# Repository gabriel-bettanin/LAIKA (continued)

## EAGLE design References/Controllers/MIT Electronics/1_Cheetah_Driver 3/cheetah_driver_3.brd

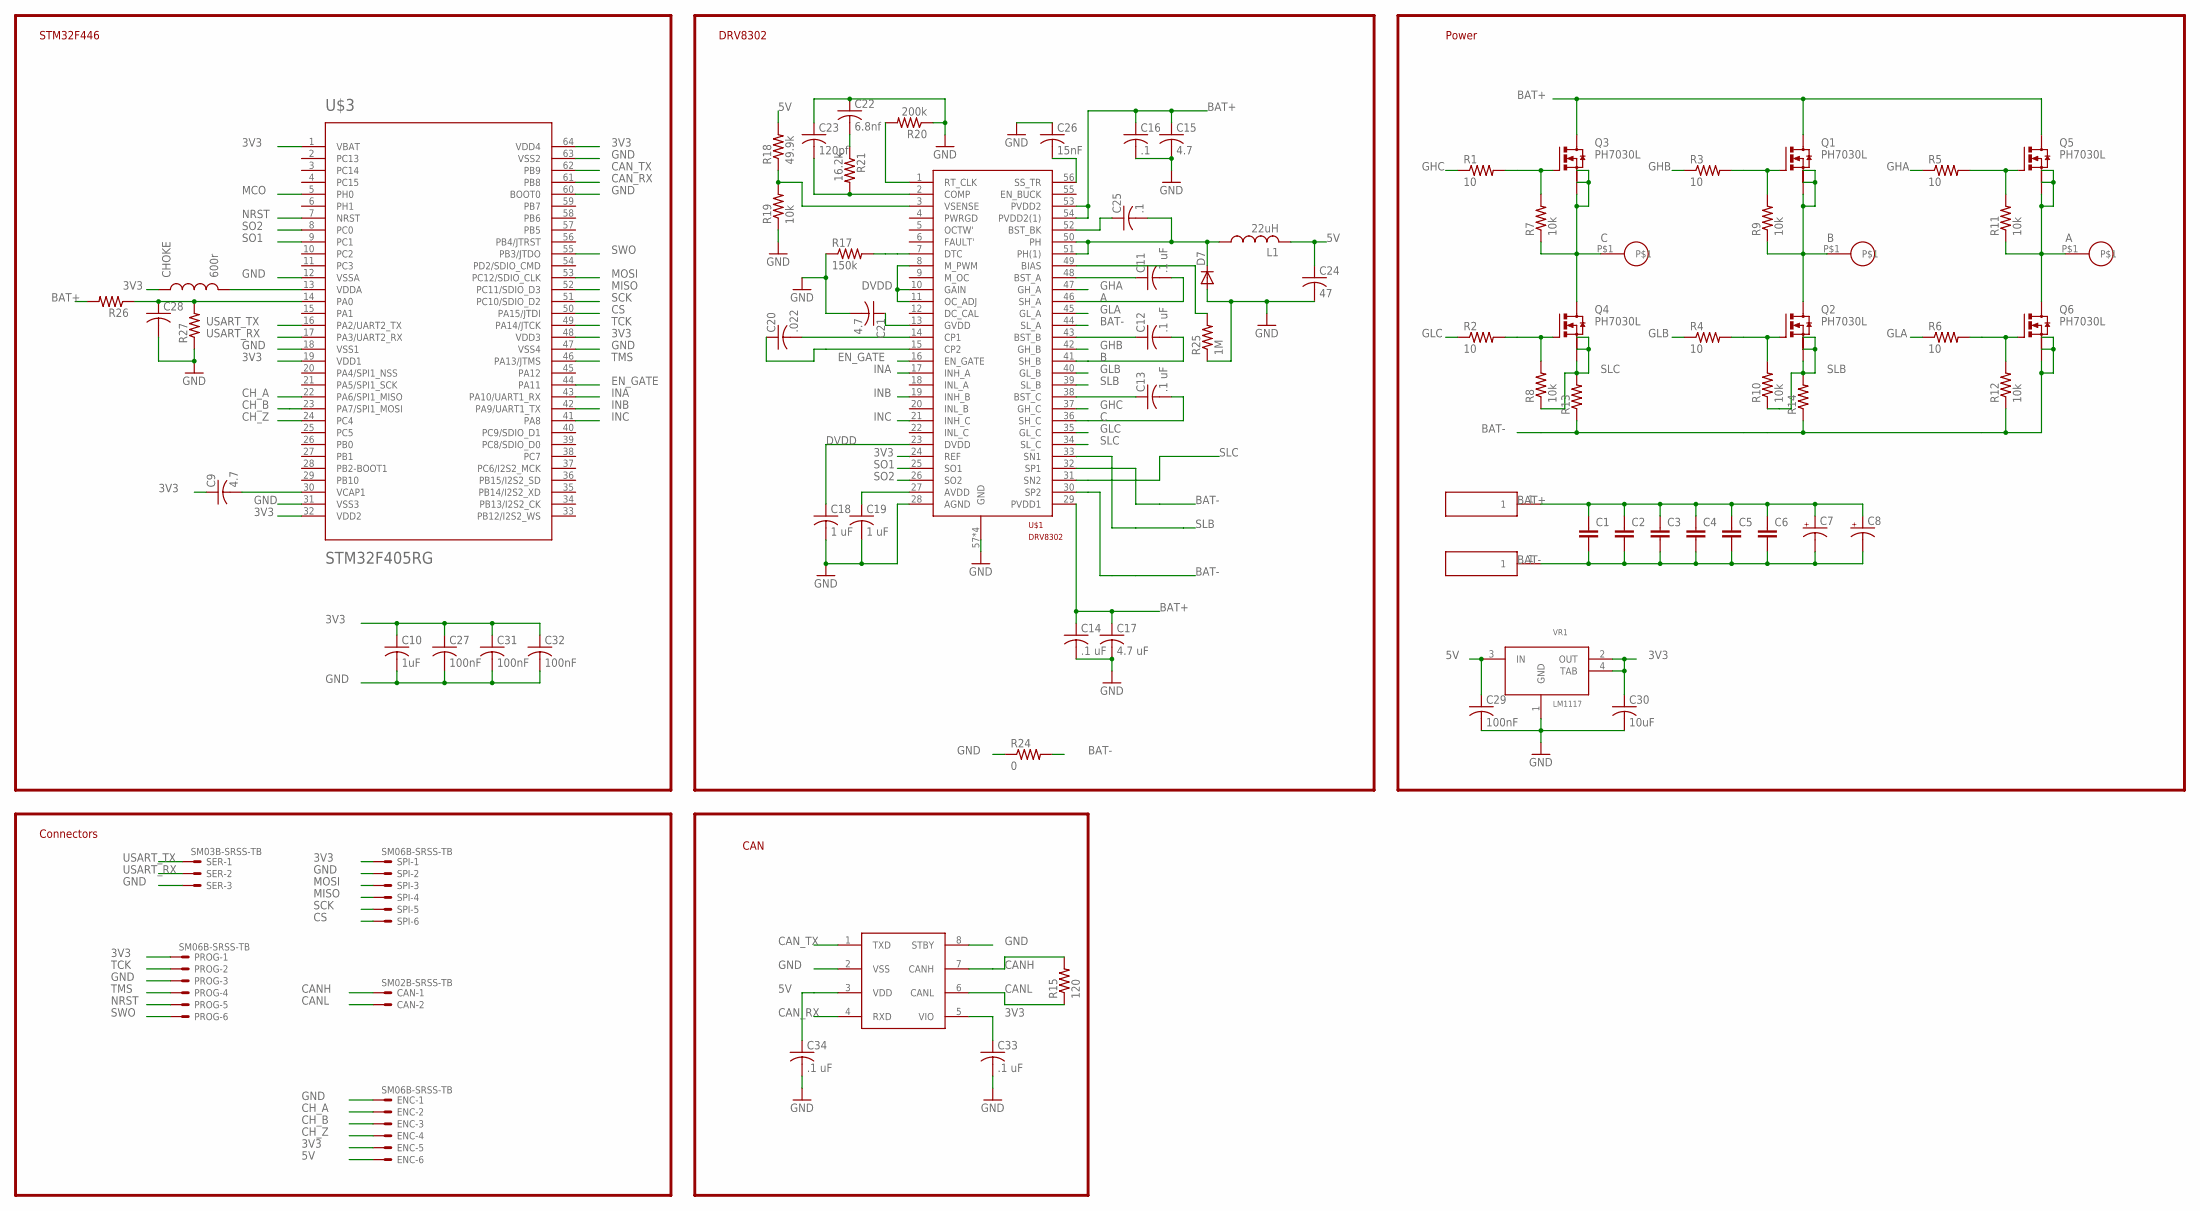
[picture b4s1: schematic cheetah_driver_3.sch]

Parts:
C1, C2, C3, C4, C5, C6: C-EUC0805; C0805
C7, C8: CPOL-USE3.5-8; E3,5-8
C9: 4.7; C0603
C10: 1uF; C0603
C11, C12, C13, C14: .1 uF; C0603
C15, C21: 4.7; C0805
C16, C25: .1; C0603
C17: 4.7 uF; C0805
C18, C19: 1 uF; C0603
C20: .022; C0603
C22: 6.8nf; C0603
C23: 120pf; C0603
C24: 47; C1210
C26: 15nF; C0603
C27, C29, C31, C32: 100nF; C0603
C28: C-USC0603; C0603
C30: 10uF; C0603
C33, C34: .1 uF; C0603K
CAN: SM02B-SRSS-TB
CHOKE: 600r; 0603
D7: DIODE-DO-214AC; DO-214AC
ENC: SM06B-SRSS-TB
J4, J5: 0.125_PAD
L1: 22uH; L4532P
PROG: SM06B-SRSS-TB
Q1, Q2, Q3, Q4, Q5, Q6: PH7030L; SOT669
R1, R2, R3, R4, R5, R6: 10; R0603
R7, R8, R9, R10, R11, R12, R19: 10k; R0603
R13, R14: R-US_R1210; R1210
R15: 120; R0603
R17: 150k; R0603
R18: 49.9k; R0603
R20: 200k; R0603
R21: 16.2k; R0603
R24: 0; R0603
R25: 1M; R0603
R26, R27: R-US_R0603; R0603
SER: SM03B-SRSS-TB
SPI: SM06B-SRSS-TB
U$1: DRV8302; HTSSOP56
U$2, U$4, U$5: 18_AWG_PAD
U$3: STM32F405RG; TQFP64
U$6: MCP2561; SO08
VR1: LM1117; SOT-223

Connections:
3V3: C9.1, C10.1, C27.1, C30.1, C31.1, C32.1, C33.1, CHOKE.1, ENC.5, PROG.1, SPI.1, U$1.24 (REF), U$3.1 (VBAT), U$3.19 (VDD1), U$3.32 (VDD2), U$3.48 (VDD3), U$3.64 (VDD4), U$6.5 (VIO), VR1.2 (OUT), VR1.4 (TAB)
5V: C24.1, C29.1, C34.1, ENC.6, L1.2, R18.2, U$6.3 (VDD), VR1.3 (IN)
A: C11.2, Q5.1 (S), Q5.2 (S), Q5.3 (S), Q6.MB (D), R11.1, U$1.46 (SH_A), U$5.P$1
B: C12.2, Q1.1 (S), Q1.2 (S), Q1.3 (S), Q2.MB (D), R9.1, U$1.41 (SH_B), U$4.P$1
BAT+: C1.1, C2.1, C3.1, C4.1, C5.1, C6.1, C7.+, C8.+, C14.1, C15.1, C16.1, C17.1, J4.1, Q1.MB (D), Q3.MB (D), Q5.MB (D), R26.2, U$1.29 (PVDD1), U$1.53 (PVDD2), U$1.54 (PVDD2(1))
BAT-: C1.2, C2.2, C3.2, C4.2, C5.2, C6.2, C7.-, C8.-, J5.1, Q6.1 (S), Q6.2 (S), Q6.3 (S), R12.1, R13.1, R14.1, R24.2, U$1.30 (SP2), U$1.32 (SP1), U$1.44 (SL_A)
C: C13.2, Q3.1 (S), Q3.2 (S), Q3.3 (S), Q4.MB (D), R7.1, U$1.36 (SH_C), U$2.P$1
CANH: CAN.1, R15.2, U$6.7 (CANH)
CANL: CAN.2, R15.1, U$6.6 (CANL)
CAN_RX: U$3.61 (PB8), U$6.4 (RXD)
CAN_TX: U$3.62 (PB9), U$6.1 (TXD)
CH_A: ENC.2, U$3.22 (PA6/SPI1_MISO)
CH_B: ENC.3, U$3.23 (PA7/SPI1_MOSI)
CH_Z: ENC.4, U$3.24 (PC4)
CS: SPI.6, U$3.50 (PA15/JTDI)
DVDD: C18.1, U$1.8 (M_PWM), U$1.10 (GAIN), U$1.11 (OC_ADJ), U$1.23 (DVDD)
EN_GATE: U$1.16 (EN_GATE), U$3.44 (PA11)
GHA: R5.1, U$1.47 (GH_A)
GHB: R3.1, U$1.42 (GH_B)
GHC: R1.1, U$1.37 (GH_C)
GLA: R6.1, U$1.45 (GL_A)
GLB: R4.1, U$1.40 (GL_B)
GLC: R2.1, U$1.35 (GL_C)
GND: C10.2, C14.2, C15.2, C16.2, C17.2, C18.2, C19.2, C21.2, C22.1, C23.1, C24.2, C26.1, C27.2, C28.2, C29.2, C30.2, C31.2, C32.2, C33.2, C34.2, D7.A, ENC.1, PROG.3, R17.1, R19.1, R20.1, R24.1, R25.1, R27.1, SER.3, SPI.2, U$1.28 (AGND), U$1.57 (GND), U$1.P$1 (GND), U$1.P$2 (GND), U$1.P$3 (GND), U$3.12 (VSSA), U$3.18 (VSS1), U$3.31 (VSS3), U$3.47 (VSS4), U$3.60 (BOOT0), U$3.63 (VSS2), U$6.2 (VSS), U$6.8 (STBY), VR1.1 (GND)
INA: U$1.17 (INH_A), U$3.43 (PA10/UART1_RX)
INB: U$1.19 (INH_B), U$3.42 (PA9/UART1_TX)
INC: U$1.21 (INH_C), U$3.41 (PA8)
MCO: U$3.5 (PH0)
MISO: SPI.4, U$3.52 (PC11/SDIO_D3)
MOSI: SPI.3, U$3.53 (PC12/SDIO_CLK)
unnamed: Q3.4 (G), R1.2, R7.2
unnamed: CHOKE.2, U$3.13 (VDDA)
unnamed: C9.2, U$3.30 (VCAP1)
unnamed: C11.1, U$1.48 (BST_A)
unnamed: R25.2, U$1.49 (BIAS)
unnamed: C13.1, U$1.38 (BST_C)
unnamed: Q4.4 (G), R2.2, R8.2
unnamed: Q1.4 (G), R3.2, R9.2
unnamed: C12.1, U$1.43 (BST_B)
unnamed: Q5.4 (G), R5.2, R11.2
unnamed: Q6.4 (G), R6.2, R12.2
unnamed: R18.1, R19.2, U$1.3 (VSENSE)
unnamed: R17.2, U$1.7 (DTC)
unnamed: C19.1, U$1.27 (AVDD)
unnamed: C20.2, U$1.14 (CP1)
unnamed: C20.1, U$1.15 (CP2)
unnamed: C21.1, U$1.13 (GVDD)
unnamed: C23.2, R21.2, U$1.2 (COMP)
unnamed: R20.2, U$1.1 (RT_CLK)
unnamed: C22.2, R21.1
unnamed: C25.2, D7.C, L1.1, U$1.50 (PH), U$1.51 (PH(1))
unnamed: C25.1, U$1.52 (BST_BK)
unnamed: C26.2, U$1.56 (SS_TR)
unnamed: C28.1, R26.1, R27.2, U$3.14 (PA0)
unnamed: Q2.4 (G), R4.2, R10.2
NRST: PROG.5, U$3.7 (NRST)
SCK: SPI.5, U$3.51 (PC10/SDIO_D2)
SLB: Q2.1 (S), Q2.2 (S), Q2.3 (S), R10.1, R14.2, U$1.33 (SN1), U$1.39 (SL_B)
SLC: Q4.1 (S), Q4.2 (S), Q4.3 (S), R8.1, R13.2, U$1.31 (SN2), U$1.34 (SL_C)
SO1: U$1.25 (SO1), U$3.9 (PC1)
SO2: U$1.26 (SO2), U$3.8 (PC0)
SWO: PROG.6, U$3.55 (PB3/JTDO)
TCK: PROG.2, U$3.49 (PA14/JTCK)
TMS: PROG.4, U$3.46 (PA13/JTMS)
USART_RX: SER.2, U$3.17 (PA3/UART2_RX)
USART_TX: SER.1, U$3.16 (PA2/UART2_TX)

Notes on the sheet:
DRV8302
STM32F446
Connectors
Power
CAN

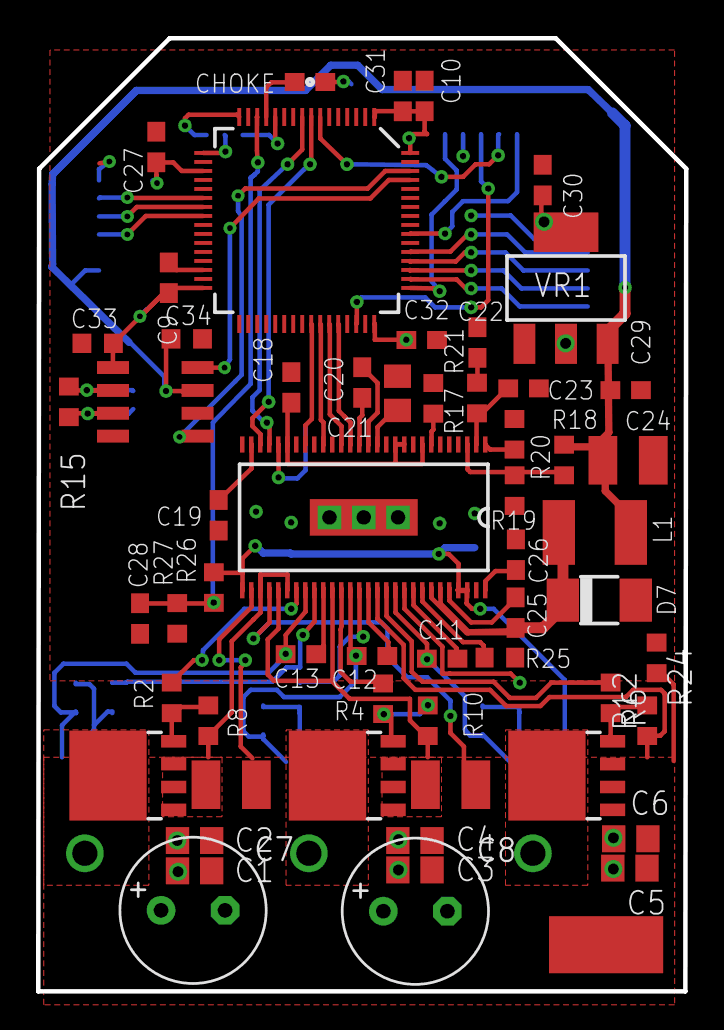
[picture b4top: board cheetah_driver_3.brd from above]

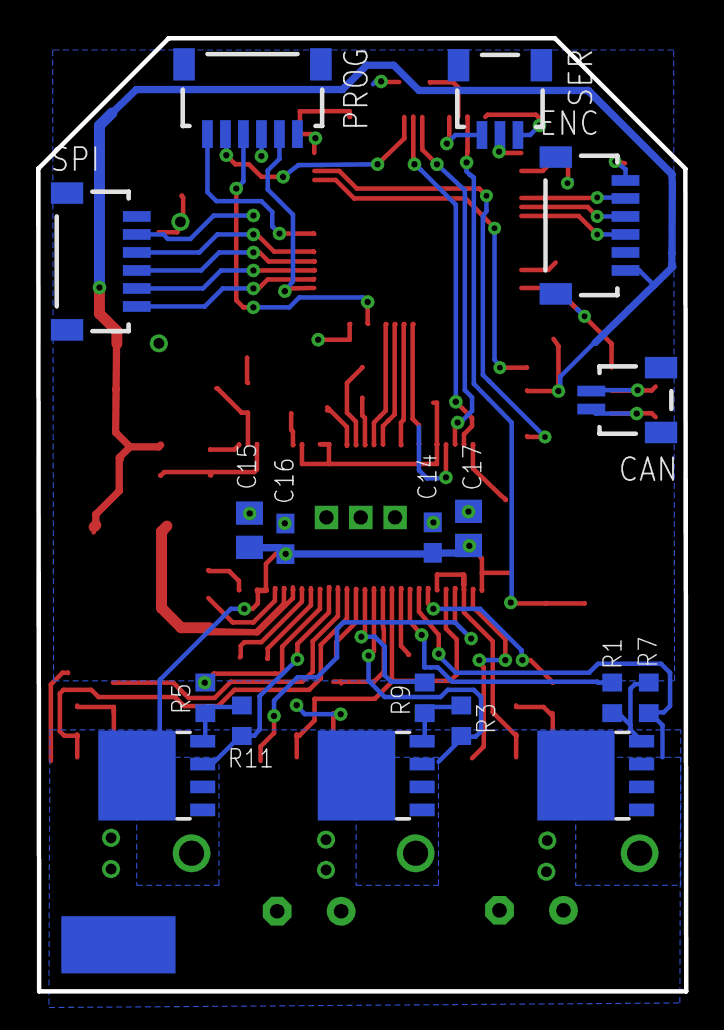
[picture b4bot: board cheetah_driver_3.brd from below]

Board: 2 copper layers, 36.0 x 52.9 mm, 81 parts (19 on the bottom side), 65 nets.
